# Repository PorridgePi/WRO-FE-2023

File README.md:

# WRO 2023 Future Engineers

# Team Information

Team ID: `FE0901`

Team Name: `raffles institution team 3`

Team Members
- [Yikun](https://github.com/PorridgePi)
- [Zachary](https://github.com/Zachareeeeee)

# Overview

Welcome to the GitHub repository for Team `FE0901` participating in WRO 2023. In this competition, we are building an autonomous robotic vehicle capable of completing 2 different challenges. This README provides a simple overview. If you wish to delve deeper into our engineering process, please check out our [Engineering Journal](docs/Engineering%20Journal.md) or [download it as PDF](https://github.com/PorridgePi/WRO-FE-2023/blob/main/docs/Engineering%20Journal.pdf).

## Demo

A demonstration video of our robot in action can be found on YouTube (or in the [video.md](video/video.md) file): [https://youtu.be/pbWbQL5pThI](https://youtu.be/pbWbQL5pThI)

### Key Timestamps
Open Challenge
- Run 1: [00:03](https://youtu.be/pbWbQL5pThI&t=3)
- Runs 2 & 3: [01:15](https://youtu.be/pbWbQL5pThI&t=75)

Obstacle Challenge:
- Run 1: [03:40](https://youtu.be/pbWbQL5pThI&t=221)

# Usage
For Code, Using Visual Studio Code:
- Clone this repository: `git clone https://github.com/PorridgePi/WRO-FE-2023`
- Change directory: `cd ./WRO-FE-2023/`
- Initialise Git submodule(s): `git submodule update --init --recursive`
- Open the repository in VSCode: `code ./`
- Install the PlatformIO plugin
- Select the appropriate PlatformIO Environment
- Use the PlatformIO plugin to compile and upload code onto the microcontroller (Raspberry PI Pico)

For Camera (OpenMV): Using the [OpenMV IDE](https://openmv.io/pages/download)
- Open the camera code (`src/omv_main.py`) in OpenMV IDE
- Upload code onto OpenMV by:
    - Select `Tools` Menu
    - Click `Save open script onto OpenMV Cam (as main.py)`

For Documentation, Using [Obsidian](https://obsidian.md/):
- Clone this repository: `git clone https://github.com/PorridgePi/WRO-FE-2023`
- Open the cloned directory as a Vault

For PCB, Using [KiCAD](https://www.kicad.org/):
- Clone this repository: `git clone https://github.com/PorridgePi/WRO-FE-2023`
- Open the file `schemes/WRO_2023/WRO_2023.kicad_pro`

# Repository Content
- `.github/workflows/platformio-ci.yml`: GitHub Actions CI workflow for PlatformIO ([Documentation](https://docs.platformio.org/en/latest/integration/ci/github-actions.html))
- `.vscode/`: Folder containing VSCode workspace settings
    - `extensions.json`: List of recommended and unwanted extensions ([Documentation](https://code.visualstudio.com/docs/editor/extension-gallery#_workspace-recommended-extensions))
- `models/`: 3D models
- `others/`: Other files
- `schemes/`: Schematic diagram and PCB
    - `WRO_2023`: PCB files that can be opened in KiCAD
- `scripts/`: Scripts for PlatformIO
    - `ci.sh`: Script for CI test
- `src/`: Main code
    - `lib/`: Libraries for components
        - Notably:
            - `lib/private/Common.h`: Shared code between `open.cpp` and `obstacle.cpp`
            - `lib/Mecha_QMC5883L`: [Forked version](https://github.com/PorridgePi/Mecha_QMC5883L) of library for the QMC5883L magnetometer
    - `test/`: Test code
    - `main.cpp`: Placeholder file
    - `obstacle.cpp`: Code for the Obstacle Challenge
    - `open.cpp`: Code for the Open Challenge
- `t-photos`: Team photo
- `v-photos`: Photos of the vehicle (from many different angles!)
- `video`: Contains [video.md](video/video.md) with the link to the video of the driving demonstration
- `.clang-format`: ClangFormat code style file - to format code in VSCode
- `.gitignore`: gitignore file ([Documentation](https://git-scm.com/docs/gitignore))
- `platformio.ini`: PlatformIO configuration file ([Documentation](https://docs.platformio.org/en/stable/projectconf/index.html))
- `README.md`: This file

# Reminders before Running
1. Calibrate compass(es)
2. Ensure steering mechanism is tightened
3. Clean wheels to ensure grip

# Hardware used
- **Motor:** 1x GM25-12CPR 
- **Servo:** 1x MG996R
- **Motor Driver:** 1x AT8236
- **Microcontroller:** 1x Raspberry Pi Pico
- **Voltage Regulator (5V):** 1x CKCS-BK-2
- **LiDAR:** 5x TF-Luna
- **Camera:** 1x OpenMV M7
- **Compass:** 1x GY-273 and 1x GY-271
- **Battery:** 1x Turnigy nano-tech 1300mAh 3S 45~90C Lipo Pack

# Continual Integration (CI) Testing

We have a simple CI testing setup with GitHub Actions, using the `scripts/ci.sh` script to automate the process of building our code for all different environments in `platformio.ini`. It checks for build success and ensures that the code can be successfully compiled.

CI is a critical aspect of our development process. It allows us to detect issues and errors in our codebase as soon as they occur. This early detection is invaluable in preventing the accumulation of errors and simplifying debugging.

Besides, our project involves multiple team members working collaboratively. CI ensures that all code changes made by different team members do not introduce regressions or break existing functionality.

To check the status of our CI, go to the [`Actions` tab](https://github.com/PorridgePi/WRO-FE-2023/actions) and view the workflow runs. If everything is going well, you should be only seeing green ticks. However, if you are seeing red crosses, something is up, but don't fret, we are definitely working hard to iron out the bugs!

(or alternatively, just look at the badge below for the CI status)

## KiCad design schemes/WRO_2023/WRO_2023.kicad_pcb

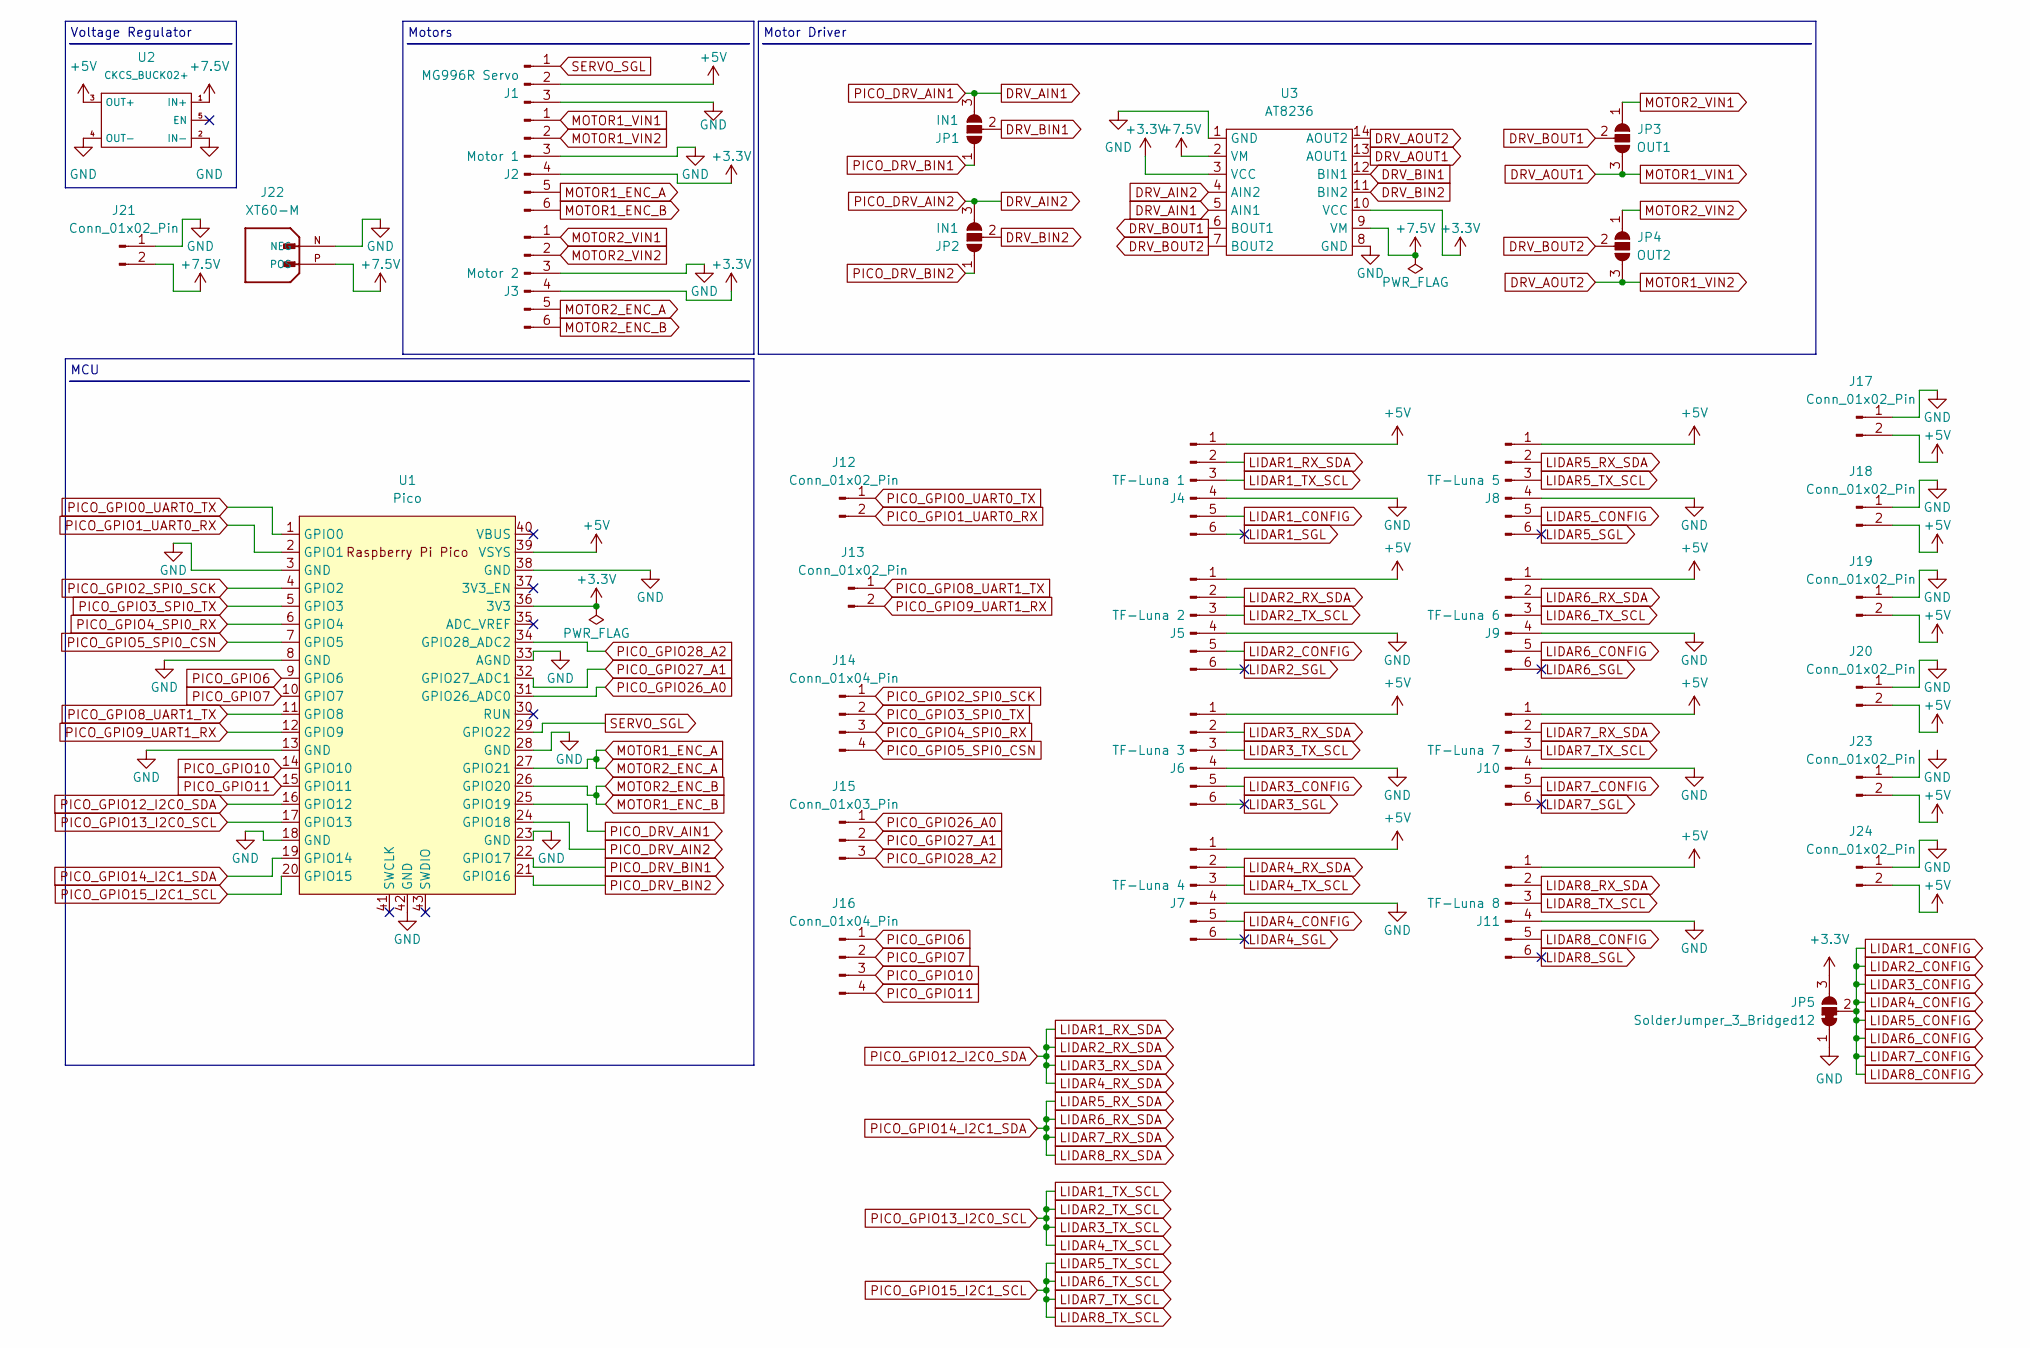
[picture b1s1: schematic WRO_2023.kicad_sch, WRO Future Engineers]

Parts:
J1: MG996R Servo; PinHeader_1x03_P2.54mm_Vertical
J2: Motor 1; PinHeader_1x06_P2.54mm_Vertical
J3: Motor 2; PinHeader_1x06_P2.54mm_Vertical
J4: TF-Luna 1; JST_XH_B6B-XH-A_1x06_P2.50mm_Vertical
J5: TF-Luna 2; JST_XH_B6B-XH-A_1x06_P2.50mm_Vertical
J6: TF-Luna 3; JST_XH_B6B-XH-A_1x06_P2.50mm_Vertical
J7: TF-Luna 4; JST_XH_B6B-XH-A_1x06_P2.50mm_Vertical
J8: TF-Luna 5; JST_XH_B6B-XH-A_1x06_P2.50mm_Vertical
J9: TF-Luna 6; JST_XH_B6B-XH-A_1x06_P2.50mm_Vertical
J10: TF-Luna 7; JST_XH_B6B-XH-A_1x06_P2.50mm_Vertical
J11: TF-Luna 8; JST_XH_B6B-XH-A_1x06_P2.50mm_Vertical
J12, J13, J17, J18, J19, J20, J21, J23, J24: Conn_01x02_Pin; JST_XH_B2B-XH-A_1x02_P2.50mm_Vertical
J14, J16: Conn_01x04_Pin; JST_XH_B4B-XH-A_1x04_P2.50mm_Vertical
J15: Conn_01x03_Pin; PinHeader_1x03_P2.54mm_Vertical
J22: XT60-M; AMASS_XT60-M; PARTREV V1.2
JP1, JP2: IN1; SolderJumper-3_P2.0mm_Open_TrianglePad1.0x1.5mm
JP3: OUT1; SolderJumper-3_P2.0mm_Open_TrianglePad1.0x1.5mm
JP4: OUT2; SolderJumper-3_P2.0mm_Open_TrianglePad1.0x1.5mm
JP5: SolderJumper_3_Bridged12; SolderJumper-3_P1.3mm_Bridged12_RoundedPad1.0x1.5mm
U1: Pico; RPi_Pico_SMD_TH
U2: CKCS_BUCK02+
U3: AT8236

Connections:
+3.3V: J2.4, J3.4, JP5.3 (B), U1.36 (3V3), U3.3 (VCC), U3.10 (VCC)
+5V: J1.2, J4.1, J5.1, J6.1, J7.1, J8.1, J9.1, J10.1, J11.1, J17.2, J18.2, J19.2, J20.2, J23.2, J24.2, U1.39 (VSYS), U2.3 (OUT+)
+7.5V: J21.2, J22.P (POS), U2.1 (IN+), U3.2 (VM), U3.9 (VM)
DRV_AIN1: JP1.3 (B), U1.25 (GPIO19), U3.5 (AIN1)
DRV_AIN2: JP2.3 (B), U1.24 (GPIO18), U3.4 (AIN2)
DRV_AOUT1: J2.1, JP3.3 (B), U3.13 (AOUT1)
DRV_AOUT2: J2.2, JP4.3 (B), U3.14 (AOUT2)
DRV_BIN1: JP1.2 (C), U3.12 (BIN1)
DRV_BIN2: JP2.2 (C), U3.11 (BIN2)
DRV_BOUT1: JP3.2 (C), U3.6 (BOUT1)
DRV_BOUT2: JP4.2 (C), U3.7 (BOUT2)
GND: J1.3, J2.3, J3.3, J4.4, J5.4, J6.4, J7.4, J8.4, J9.4, J10.4, J11.4, J17.1, J18.1, J19.1, J20.1, J21.1, J22.N (NEG), J24.1, JP5.1 (A), U1.3 (GND), U1.8 (GND), U1.13 (GND), U1.18 (GND), U1.23 (GND), U1.28 (GND), U1.33 (AGND), U1.38 (GND), U1.42 (GND), U2.2 (IN-), U2.4 (OUT-), U3.1 (GND), U3.8 (GND)
LIDAR1_CONFIG: J4.5, J5.5, J6.5, J7.5, J8.5, J9.5, J10.5, J11.5, JP5.2 (C)
LIDAR1_RX_SDA: J4.2, J5.2, J6.2, J7.2, U1.16 (GPIO12)
LIDAR1_SGL: J4.6
LIDAR1_TX_SCL: J4.3, J5.3, J6.3, J7.3, U1.17 (GPIO13)
LIDAR2_SGL: J5.6
LIDAR3_SGL: J6.6
LIDAR4_SGL: J7.6
LIDAR5_RX_SDA: J8.2, J9.2, J10.2, J11.2, U1.19 (GPIO14)
LIDAR5_SGL: J8.6
LIDAR5_TX_SCL: J8.3, J9.3, J10.3, J11.3, U1.20 (GPIO15)
LIDAR6_SGL: J9.6
LIDAR7_SGL: J10.6
LIDAR8_SGL: J11.6
MOTOR1_ENC_A: J2.5, J3.5, U1.27 (GPIO21)
MOTOR1_ENC_B: J2.6, J3.6, U1.26 (GPIO20)
MOTOR2_VIN1: J3.1, JP3.1 (A)
MOTOR2_VIN2: J3.2, JP4.1 (A)
PICO_DRV_BIN1: JP1.1 (A), U1.22 (GPIO17)
PICO_DRV_BIN2: JP2.1 (A), U1.21 (GPIO16)
PICO_GPIO0_UART0_TX: J12.1, U1.1 (GPIO0)
PICO_GPIO1_UART0_RX: J12.2, U1.2 (GPIO1)
PICO_GPIO2_SPI0_SCK: J14.1, U1.4 (GPIO2)
PICO_GPIO3_SPI0_TX: J14.2, U1.5 (GPIO3)
PICO_GPIO4_SPI0_RX: J14.3, U1.6 (GPIO4)
PICO_GPIO5_SPI0_CSN: J14.4, U1.7 (GPIO5)
PICO_GPIO6: J16.1, U1.9 (GPIO6)
PICO_GPIO7: J16.2, U1.10 (GPIO7)
PICO_GPIO8_UART1_TX: J13.1, U1.11 (GPIO8)
PICO_GPIO9_UART1_RX: J13.2, U1.12 (GPIO9)
PICO_GPIO10: J16.3, U1.14 (GPIO10)
PICO_GPIO11: J16.4, U1.15 (GPIO11)
PICO_GPIO26_A0: J15.1, U1.31 (GPIO26_ADC0)
PICO_GPIO27_A1: J15.2, U1.32 (GPIO27_ADC1)
PICO_GPIO28_A2: J15.3, U1.34 (GPIO28_ADC2)
SERVO_SGL: J1.1, U1.29 (GPIO22)

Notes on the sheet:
Voltage Regulator
Motor Driver
MCU
Motors

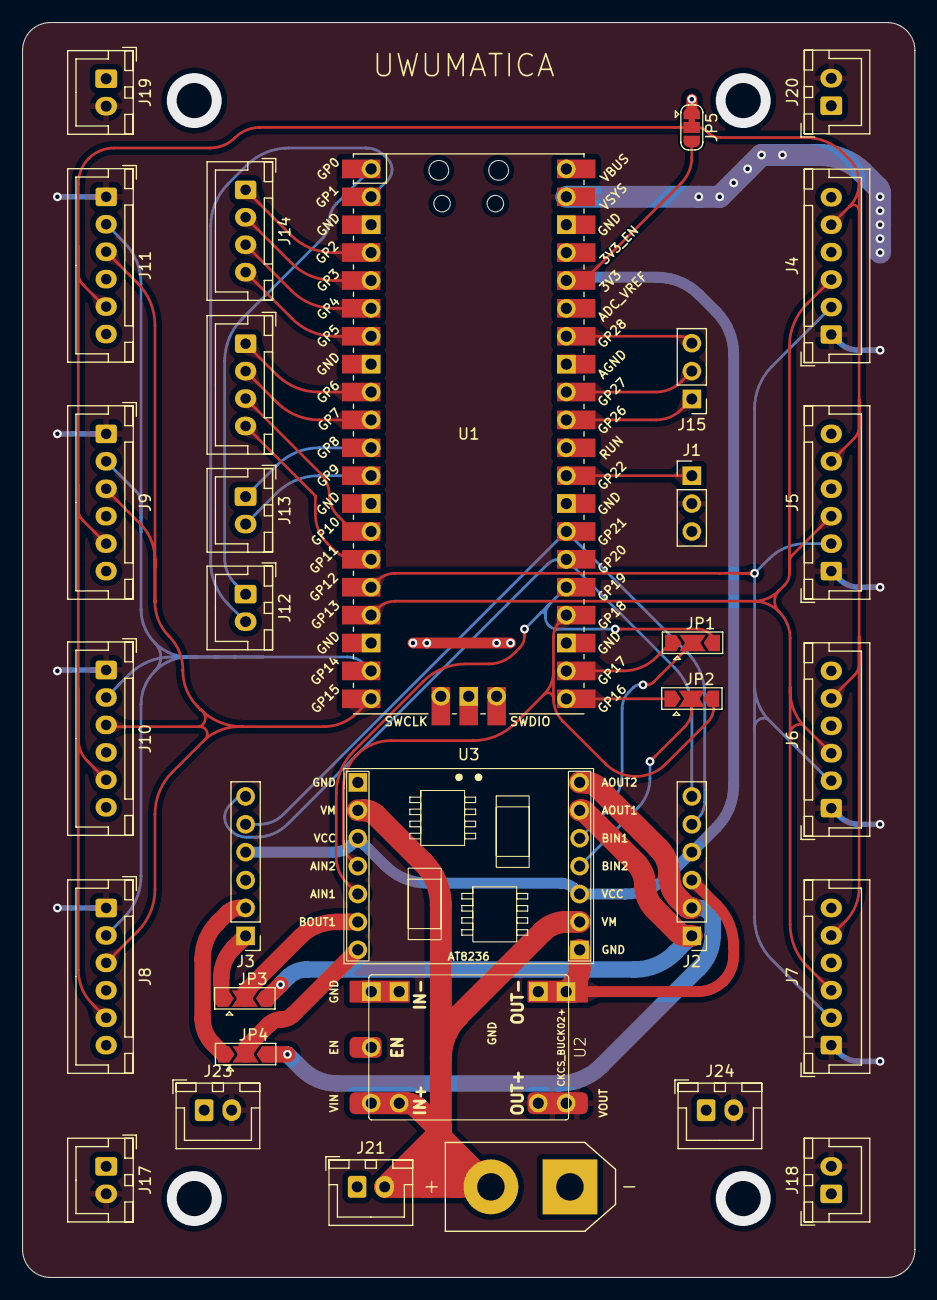
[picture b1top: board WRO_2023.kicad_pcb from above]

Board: 2 copper layers, 81.3 x 114.3 mm, 32 parts (0 on the bottom side), 39 nets.

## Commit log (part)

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2023-04-26 refactor: Rename variable names for cases
2023-04-26 chore: Delete old code
2023-04-26 gitignore: feat: Add gitignore
2023-04-26 README: feat: Add README
2023-04-26 feat: Add .clang-format
2023-04-26 platformio: feat: Add config file
2023-04-26 gitignore: feat: Add .DS_Store
2023-04-26 feat: Add initial Obsidian vault
2023-04-26 update(): 20230426-17:40
2023-04-26 update(): 20230426-17:55
2023-04-26 update(): 20230426-18:00
2023-04-26 update(): 20230426-20:36
2023-04-26 update(): 20230426-20:39
2023-04-26 update(Yikun): 20230426-20:44
2023-04-26 update(Yikun): 20230426-20:54
2023-04-27 update(Yikun): 20230427-10:29
2023-04-27 update(Yikun): 20230427-21:09
2023-05-03 update(Yikun): 20230503-21:00
2023-05-03 update: 20230503-21:08
2023-05-08 update(Yikun): 20230508-15:52
2023-05-08 update(Yikun): 20230508-15:57
2023-05-08 update(Yikun): 20230508-16:07
2023-05-08 update(Yikun): 20230508-16:17
2023-05-08 update(Zach): 20230508-16:19
2023-05-08 update(Zach): 20230508-16:24
2023-05-08 feat: Add helloworld
2023-05-08 update(Zach): 20230508-16:29
2023-05-08 update(Zach): 20230508-16:34
2023-05-08 gitignore: feat: Add Obsidian Workspace file
2023-05-08 chore: Remove Obsidian workspace file from Git
2023-05-08 update(Yikun): 20230508-16:42
2023-05-08 update(Yikun): 20230508-16:57
2023-05-08 update(Yikun): 20230508-17:02
2023-05-09 update(Yikun): 20230509-13:20
2023-05-09 ci: feat: Add CI test
2023-05-17 update(Yikun): 20230517-14:33
2023-05-17 platformio: feat: Add libraries in config
2023-05-18 update(Yikun): 20230518-08:22
2023-05-18 update(Yikun): 20230518-09:14
2023-05-23 update(): 20230523-12:36
2023-05-23 update(Yikun): 20230523-12:45
2023-05-23 feat: Add Definitions.h
2023-05-23 feat: Add I2C scanner
2023-06-05 README: feat: Add Usage information
2023-06-05 update(Yikun): 20230605-17:03
2023-06-05 update(Yikun): 20230605-17:08
2023-06-05 update(Yikun): 20230605-18:37
2023-06-19 feat: Add pico test file
2023-06-19 lib: feat: Add CommonUtils.h with macros
2023-06-20 test: feat: Add LED blink
2023-06-25 refactor: Move lib/ folder to nest under src/
2023-06-25 feat: Add public lib folder
2023-06-25 feat: Add video folder
2023-06-25 feat: Add team photos folder
2023-06-25 feat: Add models folder
2023-06-25 feat: Add schemes folder
2023-06-25 feat: Add others folder
2023-07-01 README: feat: Updated repo contents
2023-07-01 update(Yikun): 20230701-15:22
2023-07-14 test: feat: Add servo test code
2023-07-17 feat: Add if defined condition in Definitions.h
2023-07-17 feat: Add motor test code for 2 different drivers
2023-07-24 test: feat: Add motor encoder test for protoboard
2023-07-27 feat(lib): Add Lidar library
2023-07-27 feat: Automate scanning both I2C bus for I2C scanner
2023-08-01 feat: Add init for LED pin by setting pinMode
2023-08-04 feat(test): Add test code for encoder library
2023-08-04 feat(lib): Add DriveServo library
2023-08-04 feat(test): Add DriveServo library test code
2023-08-04 fix: Update platformio.ini
2023-08-04 feat(test): Add test code for Motor library
2023-08-04 feat(lib): Add Button library
2023-08-04 feat(test): Add test code for Button library
2023-08-04 feat: Add button pins to Definitions.h
2023-08-04 refactor(test): Use defined macro instead of pin integers
2023-08-04 feat(test): Add test code for motor and encoder combined
2023-08-04 feat(lib): Add QMC5883L library as submodule
2023-08-04 feat: Update QMC5883L library to work with PlatformIO
2023-08-04 feat: Add QMC5883L library in PlatformIO config
2023-08-04 feat(test): Add Lidar library test code
2023-08-11 chore: Update submodule
2023-08-11 chore: Remove debug print
2023-08-11 feat(test): Add different kinds of servo movements
2023-08-11 refactor: Separate setup function for components
2023-08-16 test: feat: Use interrupts when checking encoder
2023-08-16 chore: Updated IMU calibration
2023-08-16 feat: Update main code with new encoder and turning
2023-08-16 chore: Cleanup main code
2023-08-16 !feat: Drive in a square
2023-08-18 ci: fix: Remove extra wrong character
2023-08-18 feat: Add movement test code
2023-08-18 chore: Update IMU calibration values
2023-08-23 feat: Add Serial pins to Definitions.h
2023-08-24 feat: Add minimal interval between button presses
2023-08-24 feat: New DELTA_ANGLE macro and RUN_ONCE macro
2023-08-24 feat: Add new definition for front LiDAR spacing
2023-08-24 feat: Add test code for Open Challenge using only inner LiDAR
2023-08-24 feat: Add images for main colours to print
2023-08-24 platformio: fix: Add Open Challenge test code
2023-08-24 feat: Add rules and other documents
2023-08-24 !feat: Major update to code - use combination of synchronous blocking code and async state machine - rename taring functions and variables - new blocking turn function - new blocking move straight fu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
2023-08-24 update(Zach): 20230824-15:42
2023-08-24 update(Zach): 20230824-15:47
2023-08-24 update(Zach): 20230824-15:52
2023-08-24 update(Zach): 20230824-15:57
2023-08-24 update(Zach): 20230824-16:07
2023-08-24 update(Zach): 20230824-16:12
2023-08-24 update(Zach): 20230824-16:17
2023-08-24 update(Zach): 20230824-16:22
2023-08-24 update(Zach): 20230824-16:27
2023-08-24 update(Zach): 20230824-16:37
2023-08-24 update(Zach): 20230824-16:42
2023-08-24 update(Zach): 20230824-16:47
2023-08-24 update(Zach): 20230824-16:52
2023-08-24 update(Zach): 20230824-17:05
2023-08-24 update(Zach): 20230824-17:10
2023-08-24 update(Zach): 20230824-17:15
2023-08-28 feat: Add positive modulo macros
2023-08-28 feat: Update - updated IMU calibration values - reduced WALL_PRESENT_DISTANCE constant - turn on LED for blocking functions (turn and moveStraight) - fix: cos instead of sin for corrected front LiDAR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
2023-08-29 feat: Add sample code for new case
2023-08-29 feat: Add camera-based test code for open challenge
2023-08-29 update(Yikun): 20230829-09:38
2023-08-29 feat(lib): Updated Encoder library using interrupt
2023-08-29 chore: Move docs into subdirectory
2023-08-29 chore: Move images into subdirectory
2023-08-29 chore: Delete duplicate rule document
2023-08-29 [ImgBot] Optimize images
    *Total -- 1,319.25kb -> 446.73kb (66.14%)
    /others/Green.png -- 156.39kb -> 2.18kb (98.6%)
    /others/Orange.png -- 156.39kb -> 2.18kb (98.6%)
    /others/Red.png -- 156.39kb -> 2.18kb (98.6%)
    /others/Blue.png -- 156.39kb -> 2.18kb (98.6%)
    /SCR-20230508-ofqp.png -- 303.54kb -> 128.56kb (57.64%)
2023-08-29 docs: update(Yikun): 20230829-11:41
2023-08-29 chore: Rename images subdir to attachments
2023-08-29 docs: update(Yikun): 20230829-11:43
2023-08-29 docs: update(Yikun): 20230829-11:48
2023-08-29 docs: update(Yikun): 20230829-12:09
2023-08-29 chore: Delete merge conflict markers
2023-08-29 chore: Revert changes to Documentation.md
2023-08-29 chore: Replace tabs with 4 spaces
2023-08-29 chore: Delete unused file
2023-08-29 fix(lib): Actually working Encoder library using interrupts
2023-08-29 chore: Update main code for use with new Encoder library
2023-08-29 fix: Reduce distance
2023-08-29 feat: Updates - use old LiDAR readings if currently reading zero - define outer and inner distances globally - add direction parameter to turn function - set LiDAR FPS to 250 - remove moving forward 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
2023-08-29 refactor: Move common code into a separate file
2023-08-29 refactor: Rename main.cpp to open.cpp
2023-08-29 chore: Add dummy main.cpp
2023-08-29 feat: Update platformio.ini to reflect rename of main.cpp to open.cpp
2023-08-29 fix: Turn function now use tared trueAngle not the raw IMU angle
2023-08-29 docs: update(Zach): 20230829-18:45
2023-08-29 docs: update(Zach): 20230829-18:50
2023-08-30 feat: Add back LiDARs
2023-08-30 feat: Add Debug prints
2023-08-30 docs: update(Zach): 20230830-14:17
2023-08-30 docs: update(Zach): 20230830-14:22
2023-08-30 docs: update(Zach): 20230830-14:27
2023-08-30 docs: update(Zach): 20230830-14:32
2023-08-30 docs: update(Zach): 20230830-14:42
2023-08-30 docs: update(Zach): 20230830-15:01
2023-08-30 docs: update(Zach): 20230830-15:06
2023-08-30 feat: Major updates - add lidarHeading - estimate based on diff in LiDAR readings - add headingDiff - diff in relativeAngle and LiDAR heading - relativeAngle calculation using current side instead of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
2023-08-30 docs: update(Zach): 20230830-17:30
2023-08-30 docs: update(Zach): 20230830-17:35
2023-08-30 docs: update(Zach): 20230830-19:59
2023-08-30 feat: Update Common.h - update IMU calibration - add TURNING_RADIUS definition
2023-08-30 feat: Functional open challenge code - add MAX_CORNER_COUNT definition - add different move straight dependent on initial conditons for last turn - add face straight and track inner wall for last sec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
2023-08-30 docs: update(Zach): 20230830-20:04
2023-08-31 fix: Update Common.h - cleanup, organise - add comments - update IMU calibration - add DIST_BETWEEN_TWO_LIDARS definition - fix!: distances using distLeft instead of correct sides - rename variables 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
2023-09-01 docs: update(): 20230901-12:34
2023-09-01 docs: update(): 20230901-13:18
2023-09-01 feat: Update OpenMV code - init UART - updated trigger distance - use writechar instead of write
2023-09-01 feat: Update IMU calibration test code to include second IMU
2023-09-01 feat: Update open.cpp and Common.h For open.cpp: - refactor: Move setup, setup1 and loop1 to Common.h - chore: remove unused code - refactor: last corner move straight until align with origin positio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
2023-09-01 docs: chore: Cleanup documentation
2023-09-01 feat: Update README
2023-09-01 docs: update(): 20230901-15:14
2023-09-01 docs: update(): 20230901-15:19
2023-09-01 docs: update(): 20230901-16:02
2023-09-01 chore: Update IMU submodule
2023-09-01 feat: Add vehicle photos
2023-09-01 feat: Add video link and information
2023-09-01 fix: Update IMU git submodule
2023-09-01 docs: Update
2023-09-01 docs: update(): 20230901-19:13
2023-09-01 feat: Add PCB and Schematics
2023-09-01 chore: Delete unused attachments
2023-09-01 docs: Add PCB and Schematics
2023-09-01 docs: update(): 20230901-20:18
2023-09-01 docs: update(): 20230901-21:45
2023-09-01 docs: update(): 20230901-21:50
2023-09-01 docs: update(): 20230901-21:55
2023-09-01 docs: update(): 20230901-22:52
2023-09-01 docs: update(): 20230901-23:02
2023-09-01 docs: update(): 20230901-23:07
2023-09-01 docs: update(): 20230901-23:12
2023-09-01 docs: update(): 20230901-23:17
2023-09-01 ci: fix: Update IMU submodule
2023-09-01 feat: Add team photo
2023-09-01 feat: Add CI badge to README
2023-09-01 ci: Empty commit to trigger CI
2023-09-01 chore: Update Obsidian config files
2023-09-04 docs: update(): 20230904-11:35
2023-09-04 docs: update(Zach): 20230904-13:00
2023-09-05 chore: Update IMU calibration
2023-09-05 fix: Undefine definitions before redefining to remove warnings
2023-09-05 chore: Delete unused code
2023-09-05 !refactor: Open challenge code and Common.h - use goto instead of switch - a lot of cleanup and organisation and refactor yes.
2023-09-05 feat: Add vector resolution and summation for encoder distance
2023-09-05 !feat: Add obstacle code and update Common.h For Common.h: - do not print in first core - fix: camera buffer could be 0 to 3
2023-09-05 chore: Add comment to OpenMV code
2023-09-06 feat: Add absolute turning parameter
2023-09-13 chore: Set servo middle to 1500 for debug
2023-09-15 feat: Update OpenMV code
    - feat: Update red and green block thresholds
    - feat: Add actual fixed gain and white balance
    - fix: Set frame buffer to fix discontinued image bug
    - feat: Add taking photo mode
2023-09-15 feat: Update Open challenge code
    - fix: Continuously tare during start case, and add delay after button press
    - refactor: Use updated turn function
    - fix: Slow down for last corner to get accurate front LiDAR readings
    - fix: Remove faceStraight function - causing robot to not stop
    - fix: Use 100cm instead of 70cm for innerDist to prevent false trigger
    - fix: Remove encoder for last lap as it did not stop
2023-09-15 feat: Update Obstacle challenge code
    - feat: Use new turn2 function
    - fix: Continuously tare angle in start state
    - feat: Add ending condition and state - move back
2023-11-06 docs: update(Yikun): 20231106-22:24
